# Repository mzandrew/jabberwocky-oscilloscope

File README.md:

# jabberwocky-oscilloscope
an open-source & open-hardware oscilloscope

Jabberwocky is an acronym for Just Another Big Bandwidth Event Recorder With Oscilloscope Capabilities.

It is a combination of hardware designs and software that uses an ASIC switched-capacitor-array ADC to make a handheld, battery/usb powered, 2 channel oscilloscope with an OLED display.

Development on the oscilloscope was started in January, 2008. A design was finalized and a board was fabricated in May of that year.

# overview

The oscilloscope is battery (rechargable LiPoly) or usb powered, has 2 channels of input (DC coupled only), has a 128×124 pixel full-color OLED display. It supports (slightly) advanced triggering or an optional trigger-delay.

The input impedance of this scope is 1MOhm. The analog bandwidth is unknown at this point (and will be until the project is nearly complete). The lab3 can sample billions of times per second, but this oscilloscope will probably only be useful at a much much lower sampling speed. This is due to the choice of input amplifier and multiplexer: The multiplexer has a bandwidth of about 700MHz as does the voltage-feedback operational amplifier.

# files

[PCB schmatic](jabberwocky-PCB-eagle/jabberwocky.schematic.pdf)

[PCB layout](jabberwocky-PCB-eagle/jabberwocky.layout.pdf)

[PCB gerber files](jabberwocky-PCB-eagle/arm7-oscilloscope-gerbers.zip)

# notes

Automatically exported from code.google.com/p/jabberwocky-oscilloscope

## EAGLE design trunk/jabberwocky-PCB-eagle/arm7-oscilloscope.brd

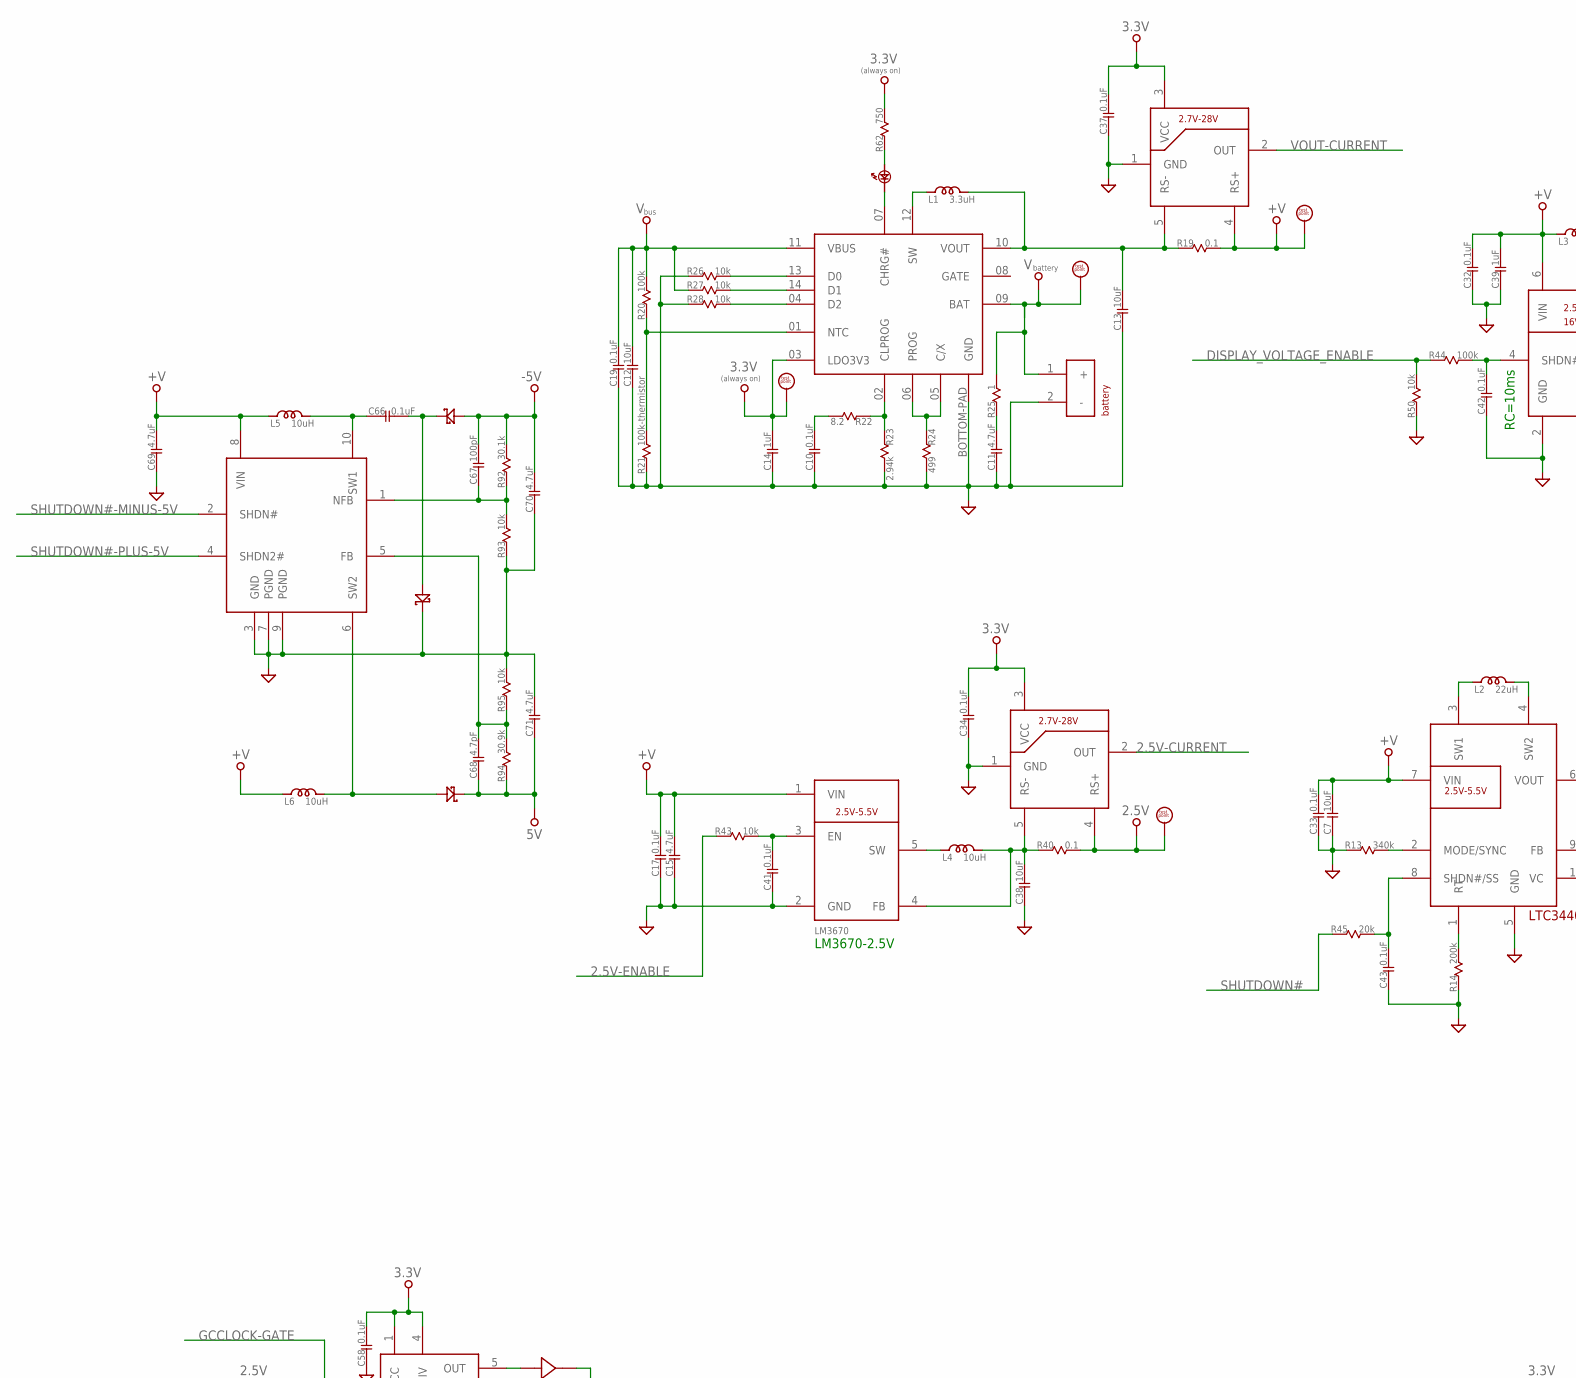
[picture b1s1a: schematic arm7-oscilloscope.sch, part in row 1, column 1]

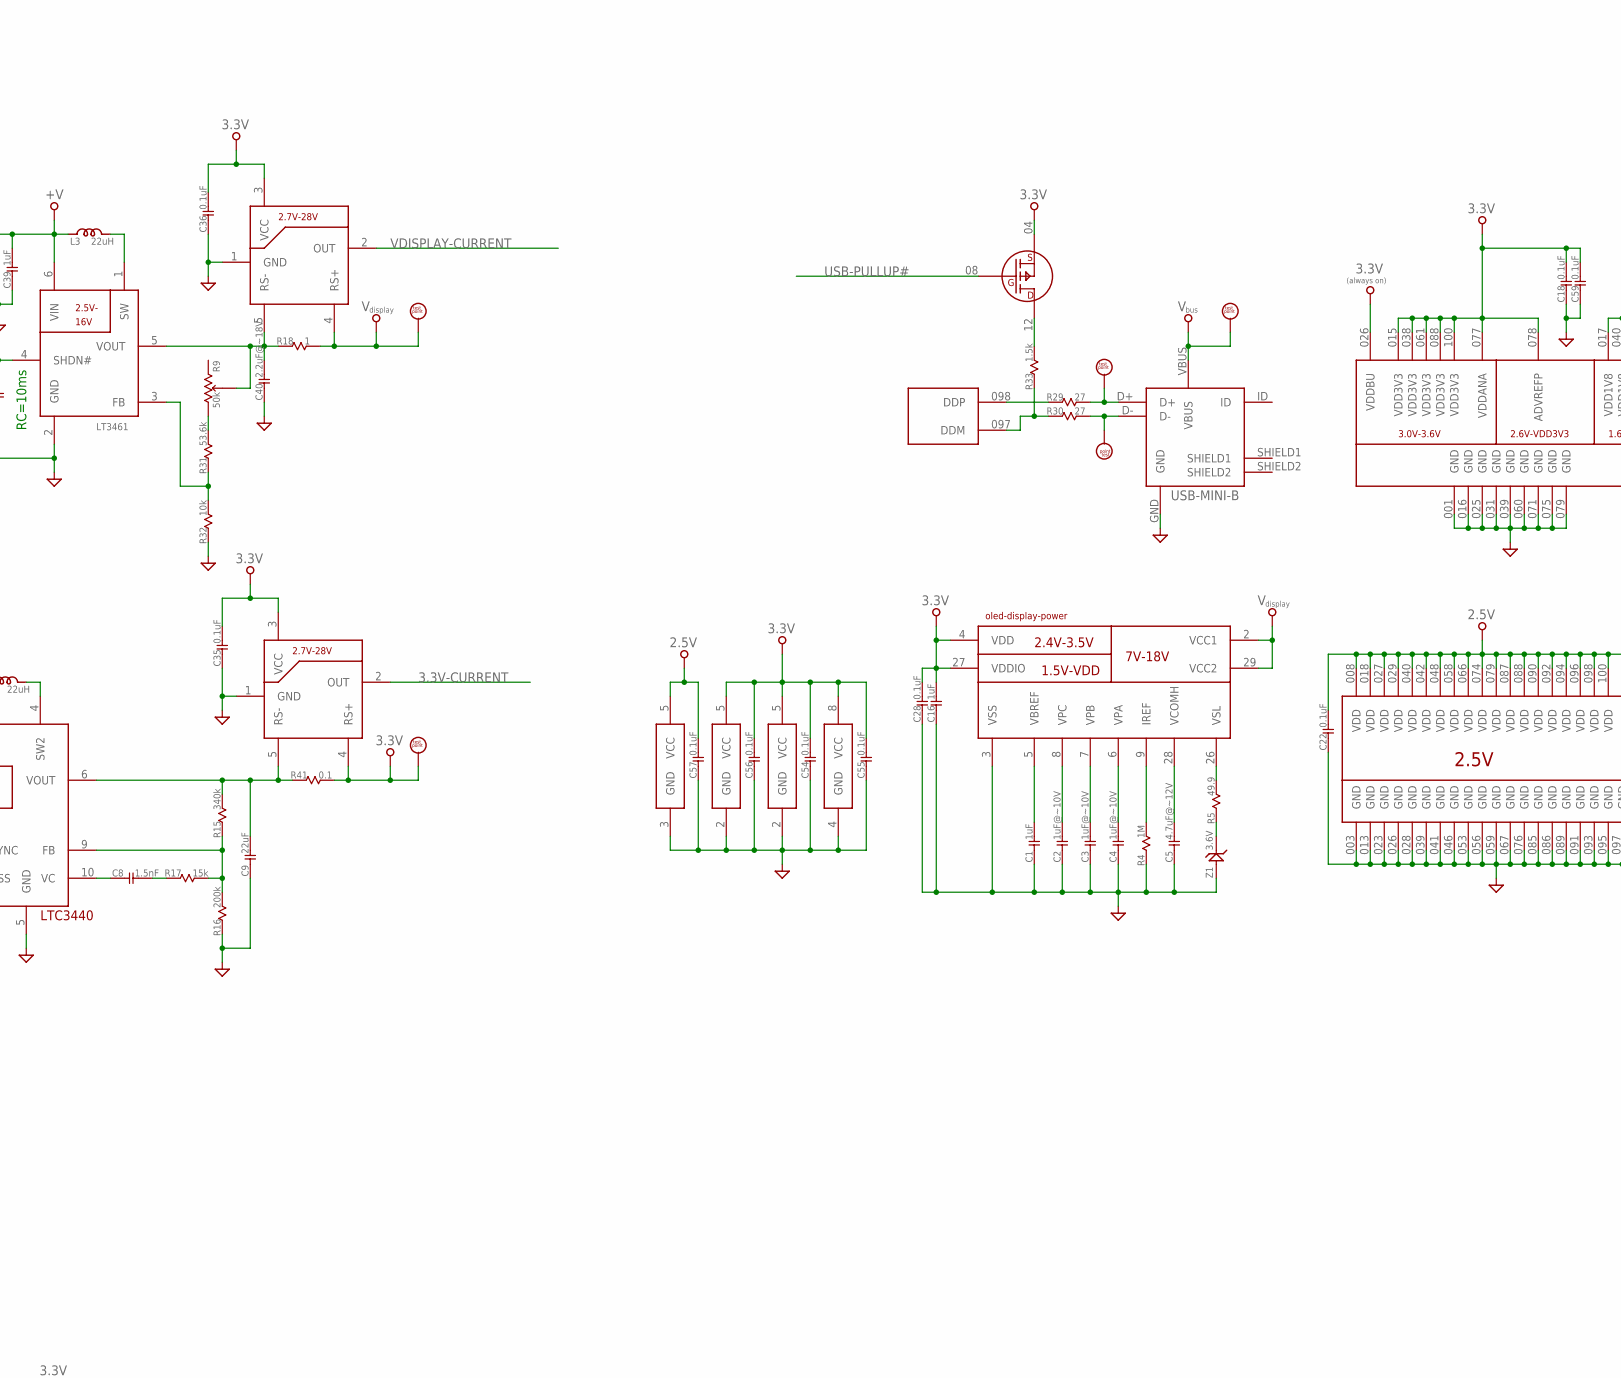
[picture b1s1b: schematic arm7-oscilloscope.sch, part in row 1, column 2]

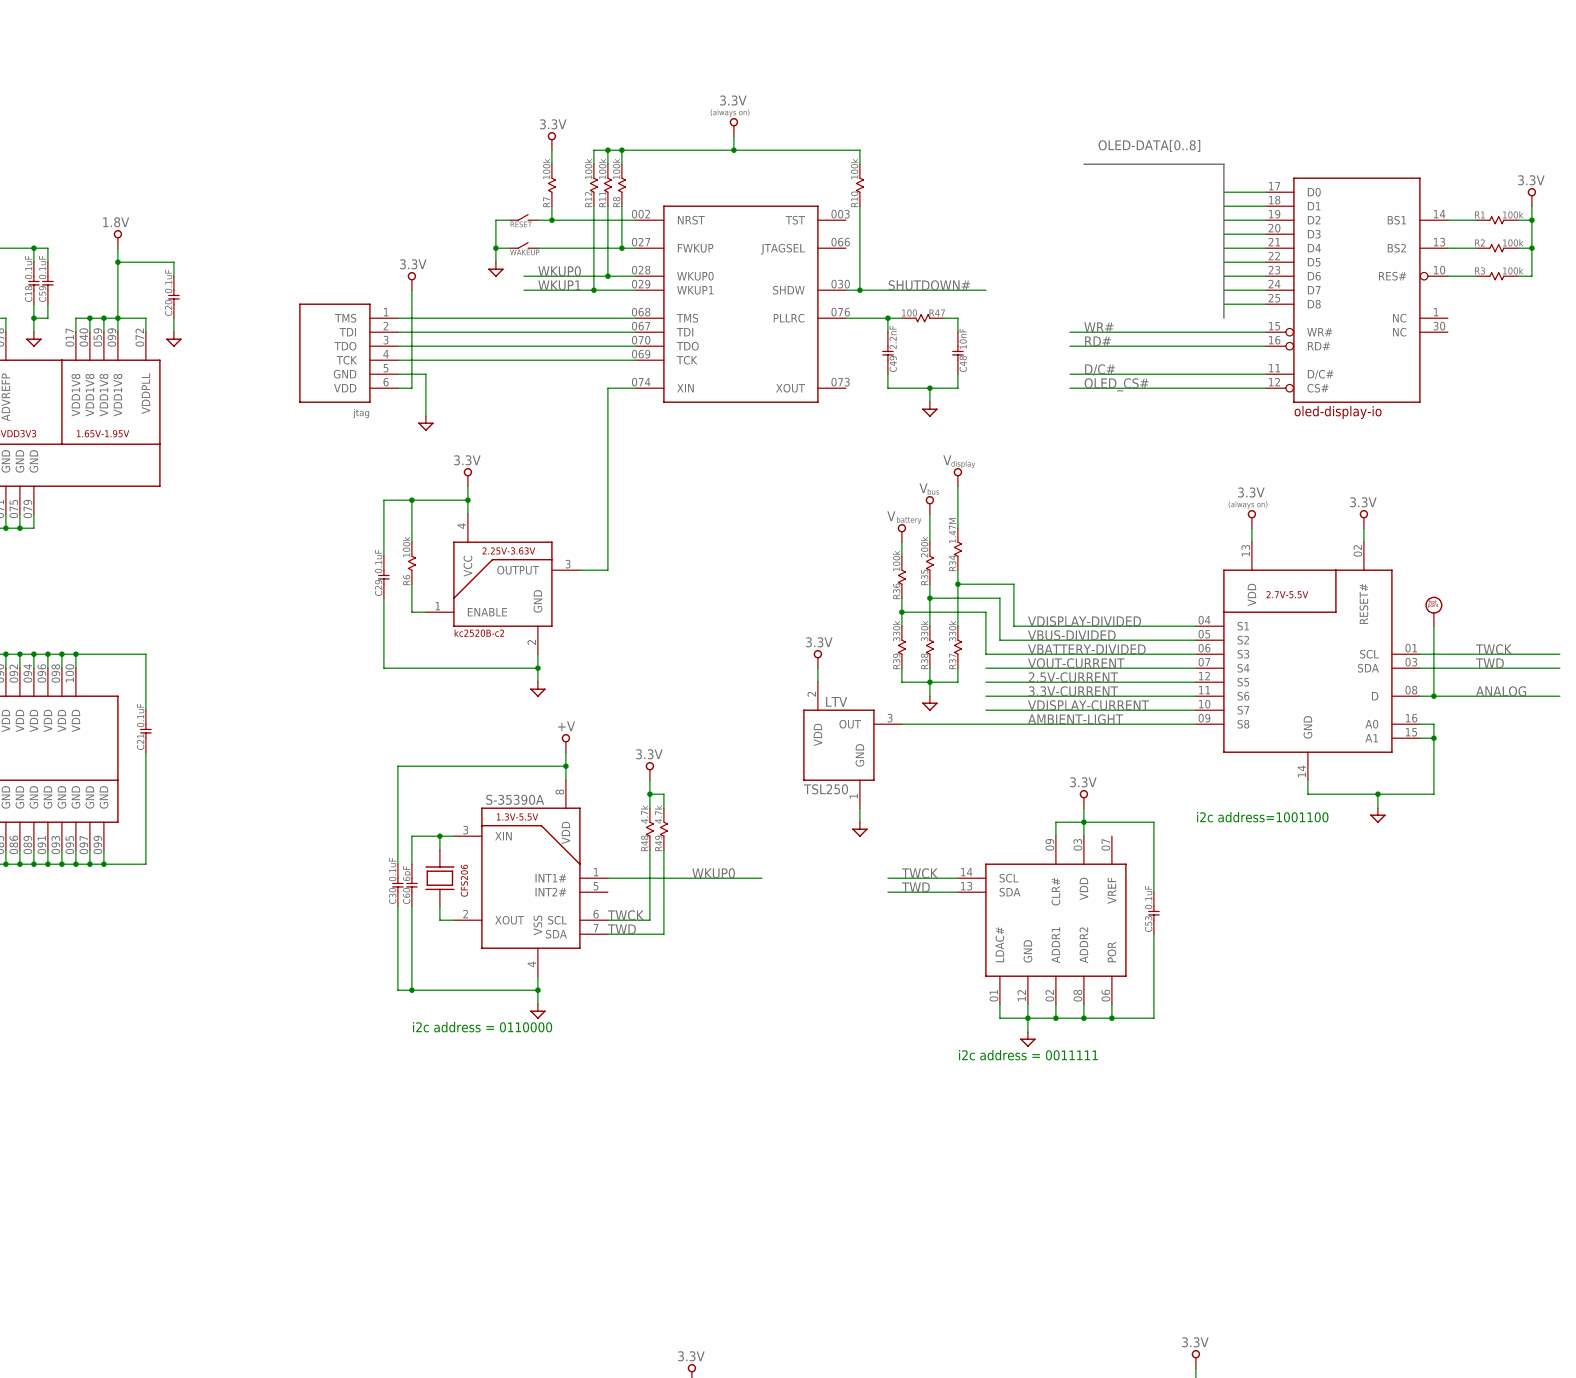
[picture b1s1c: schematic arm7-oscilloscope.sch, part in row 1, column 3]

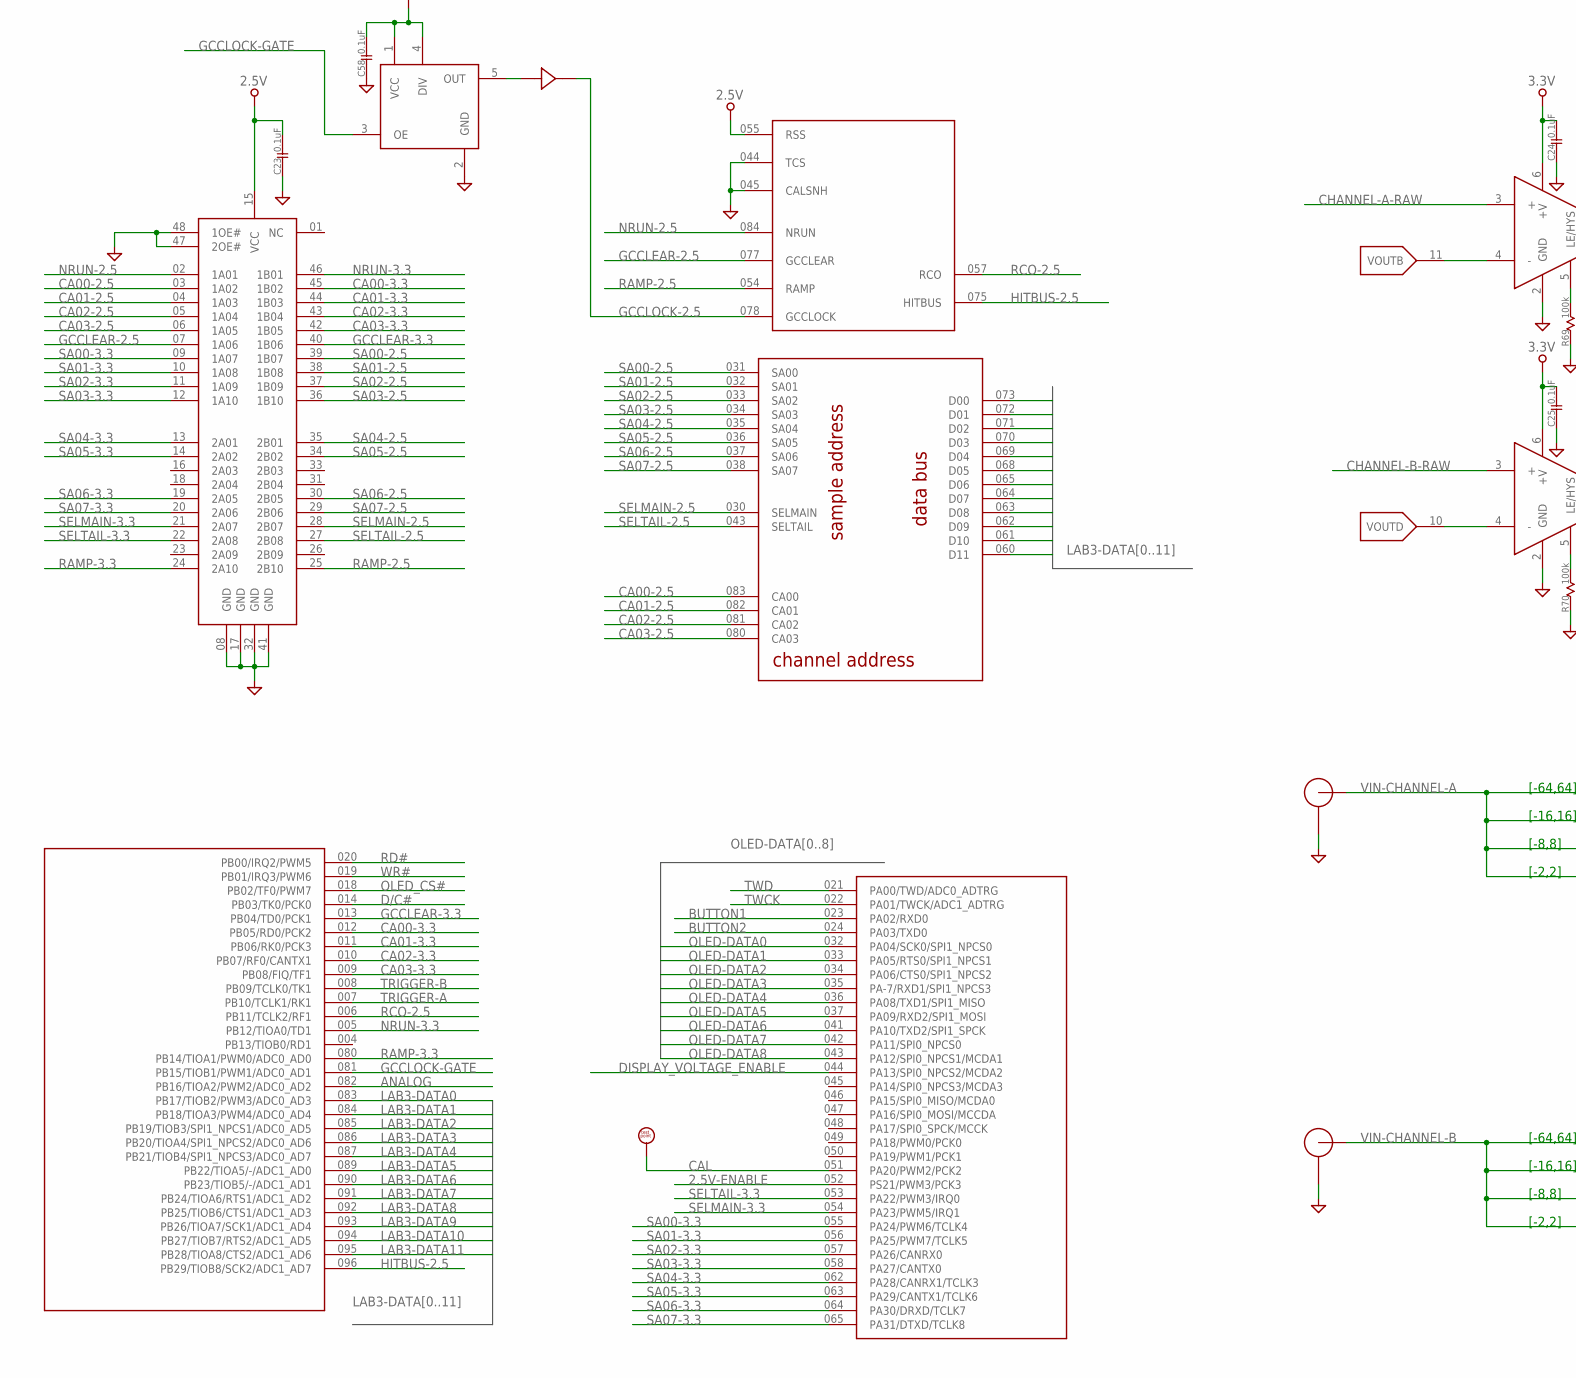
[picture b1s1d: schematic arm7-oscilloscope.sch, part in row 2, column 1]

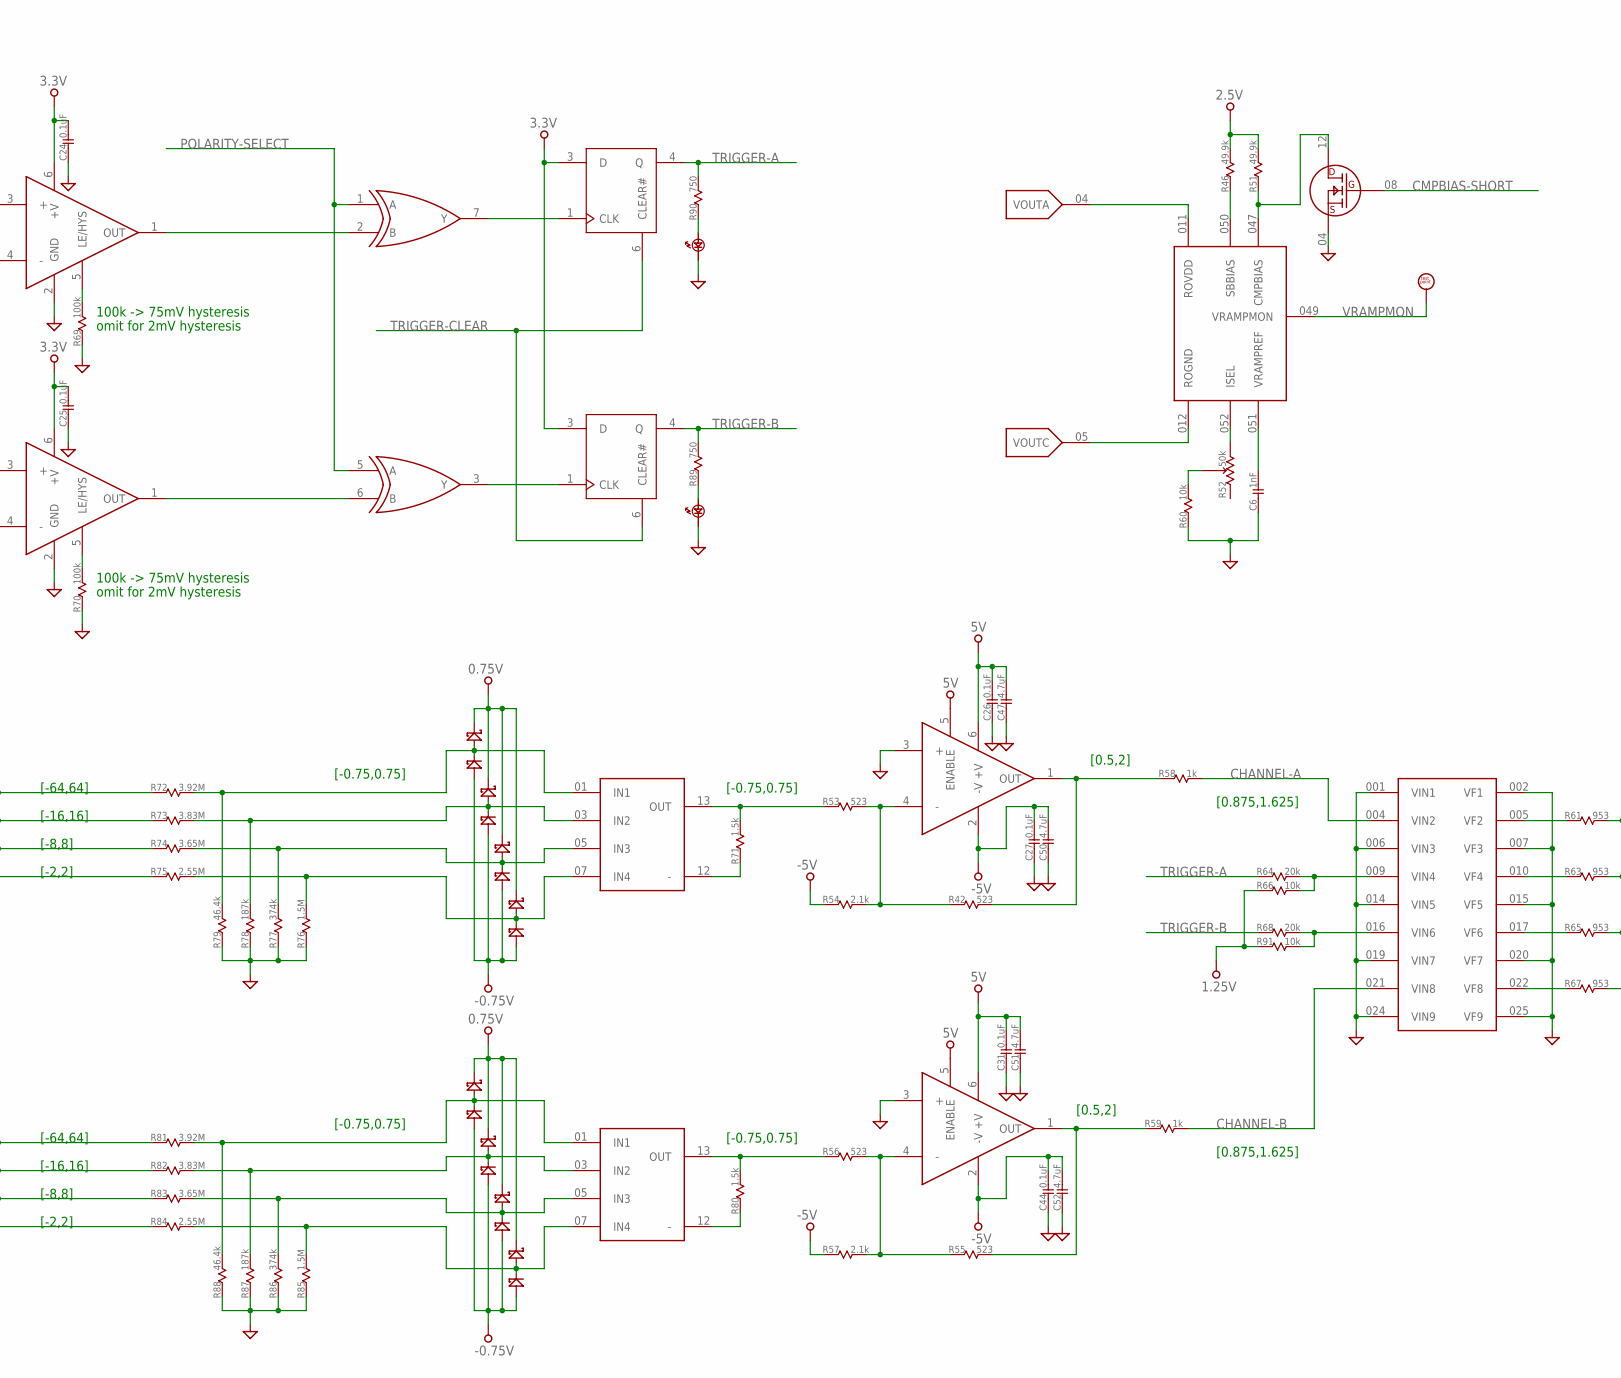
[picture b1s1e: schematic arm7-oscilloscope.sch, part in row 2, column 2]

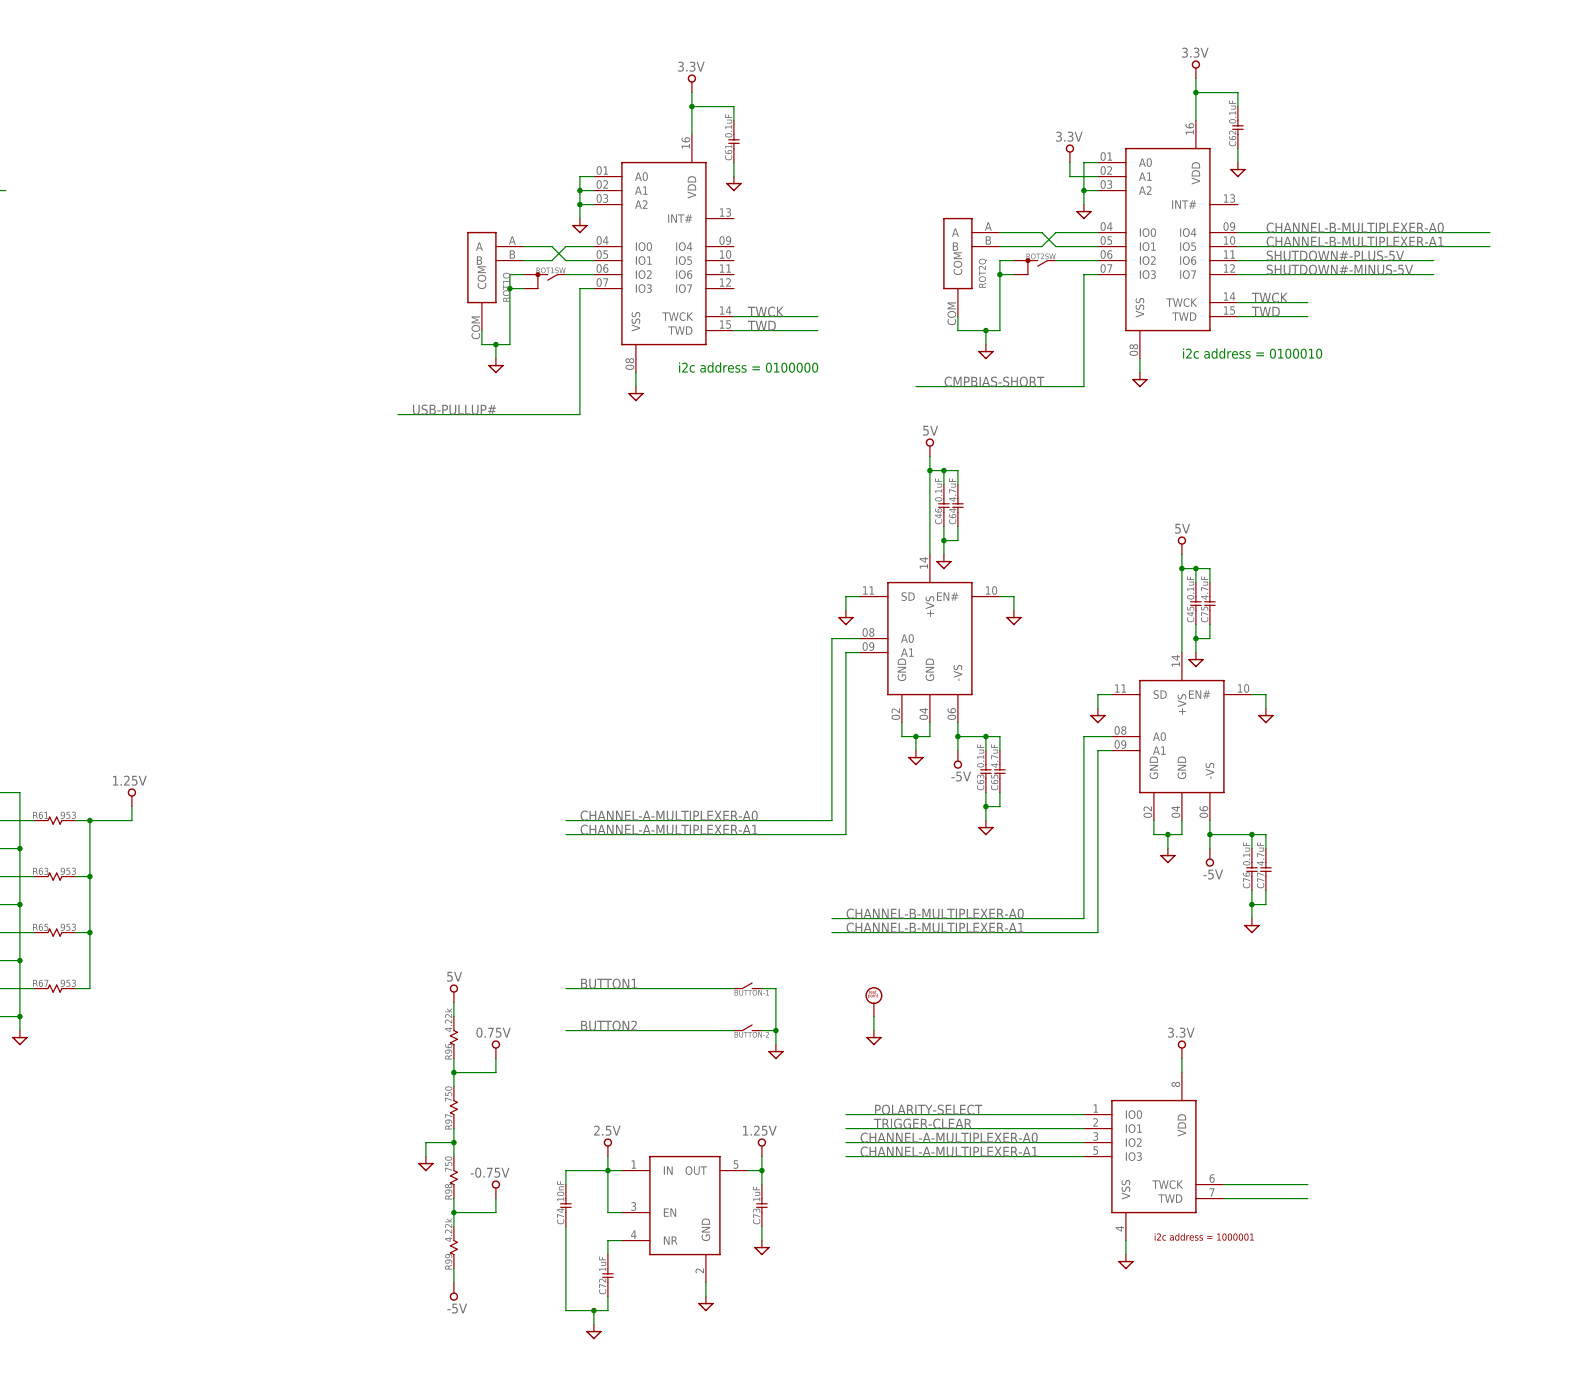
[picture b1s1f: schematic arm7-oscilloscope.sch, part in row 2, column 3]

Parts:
1.25VDC: TPS731XX; SOT-23-5
2.5V, 3.3V, 3.3V-ALWAYS: TEST-POINTSURFACE-MOUNT-1X1; TEST-POINT-SURFACE-MOUNT-1X1
2.5VDC: LM3670; SOT-23-5
3.3VDC: LTC3440; MSOP-10
4DACS: AD56X5R; TSSOP-14
7-18VDC: LT3461; SOT-23-6
+-5VDC: LT1945; MSOP-10
AMP-A: OP-AMP-SOT-23-6; SOT-23-6
AMP-B: OP-AMP-SOT-23-6; SOT-23-6
ANALOG: TEST-POINTSURFACE-MOUNT-1X1; TEST-POINT-SURFACE-MOUNT-1X1
BAT: BATTERY-ON-EXTERNAL-CONNECTOR; S2B-PH-K
BUF1: SN74LVC1G34; SC-70-5
BUTTON-1, BUTTON-2: B3U-1000P
C1, C14, C16, C39, C72, C73: 1uF; 0603
C2, C3, C4: 1uF@~10V; 0603
C5: 4.7uF@~12V; 0805
C6: 1nF; 0603
C7, C12, C13: 10uF; 0805
C8: 1.5nF; 0603
C9: 22uF; 0805
C10, C17, C18, C19, C20, C21, C22, C23, C24, C25, C26, C27, C28, C29, C30, C31, C32, C33, C34, C35, C36, C37, C41, C42, C43, C44, C45, C46, C53, C54, C55, C56, C57, C58, C59, C61, C62, C63, C66, C76: 0.1uF; 0603
C11, C15, C47, C50, C51, C52, C64, C65, C69, C70, C71, C75, C77: 4.7uF; 0603
C38: 10uF; 0603
C40: 2.2uF@~18V; 0805
C48, C74: 10nF; 0603
C49: 2.2nF; 0603
C60: 6pF; 0603
C67: 100pF; 0603
C68: 4.7pF; 0603
CAL: TEST-POINTTHROUGH-HOLE; TEST-POINT-THROUGH-HOLE
CH-A: SMA-SHORT-BARREL-SD-73251-115
CH-B: SMA-SHORT-BARREL-SD-73251-115
CHARGE: LED; 0603
CHRG: LTC4088; DFN-14
CMP-A: ADCMP601; SC-70-6
CMP-B: ADCMP601; SC-70-6
D1, D2, D3: DIODE-SCHOTTKY1005; 1005-DIODE-SCHOTTKY
D4, D5, D6, D7, D8, D9, D10, D11: DIODE-SCHOTTKY-PAIR-ANODE-TO-CATHODE; SOT-23
D+: TEST-POINTSURFACE-MOUNT-1X1; TEST-POINT-SURFACE-MOUNT-1X1
D-: TEST-POINTSURFACE-MOUNT-1X1; TEST-POINT-SURFACE-MOUNT-1X1
FET1: NDS332P; SOT-23
FET2: NDS331N; SOT-23
FFA: 74LVC1G175; SC-70-6
FFB: 74LVC1G175; SC-70-6
GND: TEST-POINTTHROUGH-HOLE; TEST-POINT-THROUGH-HOLE
GPIO1: PCA9536; MSOP-8-OR-TSSOP-8
GPIO2, GPIO3: PCA9554; TSSOP-16
JTAG: HEADER-2MM-2X3-JTAG; HEADER-2MM-2X3
L1: 3.3uH; ELL4-M
L2: 22uH; SD6030
L3: 22uH; 1007
L4, L5, L6: 10uH; 1210
LAB3: LABRADOR3; LQFP-100
LEVEL-SHIFT: SN74CB3T16210; TSSOP-48
LTV: TLS250-BENT; TSL250-BENT
MPEX: ADG728; TSSOP-16
MPEX-A: FHP3194; TSSOP-14
MPEX-B: FHP3194; TSSOP-14
OLED: OLED-DISPLAY-CONNECTOR-2TOP-CONTACTS-IN-USE; XF2M-3015-1A-TOP-CONTACTS-IN-USE
OSC1: KC2520B-C2; OSCILLATOR-2.5X2.0
OSC2: LTC6905; SOT-23-5
R1, R2, R3, R6, R7, R8, R10, R11, R12, R20, R36, R44, R69, R70: 100k; 0603
R4: 1M; 0603
R5: 49.9; 0603
R9, R52: 50k; 3313J-1
R13, R15: 340k; 0603
R14, R16, R35: 200k; 0603
R17: 15k; 0603
R18: 1; 0805
R19, R40, R41: 0.1; 0805
R21: 100k-thermistor; 0603
R22: 8.2; 0603
R23: 2.94k; 0603
R24: 499; 0603
R25: 1; 0603
R26, R27, R28, R32, R43, R50, R60, R66, R91, R93, R95: 10k; 0603
R29, R30: 27; 0603
R31: 53.6k; 0603
R33, R71, R80: 1.5k; 0603
R34: 1.47M; 0603
R37, R38, R39: 330k; 0603
R42, R53, R55, R56: 523; 0603
R45, R64, R68: 20k; 0603
R46, R51: 49.9k; 0603
R47: 100; 0603
R48, R49: 4.7k; 0603
R54, R57: 2.1k; 0603
R58, R59: 1k; 0603
R61, R63, R65, R67: 953; 0603
R62, R89, R90, R97, R98: 750; 0603
R72, R81: 3.92M; 0603
R73, R82: 3.83M; 0603
R74, R83: 3.65M; 0603
R75, R84: 2.55M; 0603
R76, R85: 1.5M; 0603
R77, R86: 374k; 0603
R78, R87: 187k; 0603
R79, R88: 46.4k; 0603
R92: 30.1k; 0603
R94: 30.9k; 0603
R96, R99: 4.22k; 0603
RESET: B3U-1000P
ROT1, ROT2: EVQWK4
RTC: S-35390A; TSSOP-8
TRIGGER-A: LED; 0603
TRIGGER-B: LED; 0603
U$41: CFS206
U$69, U$70, U$71, U$72: MAX4372; SOT-23-5
UC: AT91SAM7A3; LQFP-100
USB: USB-MINI-B; USB-MINI-B-THROUGH-HOLE
VBAT: TEST-POINTSURFACE-MOUNT-1X1; TEST-POINT-SURFACE-MOUNT-1X1
VBUS: TEST-POINTSURFACE-MOUNT-1X1; TEST-POINT-SURFACE-MOUNT-1X1
VDISP: TEST-POINTSURFACE-MOUNT-1X1; TEST-POINT-SURFACE-MOUNT-1X1
VOUT: TEST-POINTSURFACE-MOUNT-1X1; TEST-POINT-SURFACE-MOUNT-1X1
VRAMP: TEST-POINTSURFACE-MOUNT-1X1; TEST-POINT-SURFACE-MOUNT-1X1
WAKEUP: B3U-1000P
XOR: 74LVC2G86; VSSOP-8
Z1: 3.6V; 0603

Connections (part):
0.75V: D4.04 (CATHODE), D5.04 (CATHODE), D6.04 (CATHODE), D7.04 (CATHODE), D8.04 (CATHODE), D9.04 (CATHODE), D10.04 (CATHODE), D11.04 (CATHODE), R96.1, R97.2
1.8V: C20.2, UC.017 (VDD1V8), UC.040 (VDD1V8), UC.059 (VDD1V8), UC.072 (VDDPLL), UC.099 (VDD1V8)
1.25V: 1.25VDC.5 (OUT), C73.2, R61.2, R63.2, R65.2, R66.1, R67.2, R91.1
2.5V: 1.25VDC.1 (IN), 1.25VDC.3 (EN), 2.5V.1, BUF1.5 (VCC), C21.2, C22.2, C23.2, C57.2, C74.2, LAB3.008 (VDD), LAB3.018 (VDD), LAB3.027 (VDD), LAB3.029 (VDD), LAB3.040 (VDD), LAB3.042 (VDD), LAB3.048 (VDD), LAB3.055 (RSS), LAB3.058 (VDD), LAB3.066 (VDD), LAB3.074 (VDD), LAB3.079 (VDD), LAB3.087 (VDD), LAB3.088 (VDD), LAB3.090 (VDD), LAB3.092 (VDD), LAB3.094 (VDD), LAB3.096 (VDD), LAB3.098 (VDD), LAB3.100 (VDD), LEVEL-SHIFT.15 (VCC), R40.2, R46.2, R51.2, U$69.4 (RS+)
2.5V-CURRENT: MPEX.12 (S5), U$69.2 (OUT)
2.5V-ENABLE: R43.1, UC.052 (PS21/PWM3/PCK3)
3.3V: 3.3V.1, 4DACS.03 (VDD), 4DACS.09 (CLR#), C16.2, C18.2, C24.2, C25.2, C28.2, C29.2, C34.2, C35.2, C36.2, C37.2, C53.2, C54.2, C55.2, C56.2, C58.2, C59.2, C61.2, C62.2, CMP-A.6 (+V), CMP-B.6 (+V), FET1.04 (S), FFA.3 (D), FFA.5 (VCC), FFB.3 (D), FFB.5 (VCC), GPIO1.8 (VDD), GPIO2.16 (VDD), GPIO3.02 (A1), GPIO3.16 (VDD), JTAG.6 (VDD), LTV.2 (VDD), MPEX.02 (RESET#), OLED.4 (VDD), OLED.27 (VDDIO), OSC1.4 (VCC), OSC2.1 (VCC), OSC2.4 (DIV), R1.2, R2.2, R3.2, R6.2, R7.2, R41.2, R48.2, R49.2, U$69.3 (VCC), U$70.3 (VCC), U$70.4 (RS+), U$71.3 (VCC), U$72.3 (VCC), UC.015 (VDD3V3), UC.038 (VDD3V3), UC.061 (VDD3V3), UC.077 (VDDANA), UC.078 (ADVREFP), UC.088 (VDD3V3), UC.100 (VDD3V3), XOR.8 (VCC)
3.3V-ALWAYS: 3.3V-ALWAYS.1, C14.2, CHRG.03 (LDO3V3), MPEX.13 (VDD), R8.2, R10.2, R11.2, R12.2, R62.2, UC.026 (VDDBU)
3.3V-CURRENT: MPEX.11 (S6), U$70.2 (OUT)
5V: AMP-A.5 (ENABLE), AMP-A.6 (+V), AMP-B.5 (ENABLE), AMP-B.6 (+V), C26.2, C31.2, C45.2, C46.2, C47.2, C51.2, C64.2, C68.1, C71.1, C75.2, D3.P$2 (CATHODE), MPEX-A.14 (+VS), MPEX-B.14 (+VS), R94.1, R96.2
+V: 2.5VDC.1 (VIN), 3.3VDC.7 (VIN), 7-18VDC.6 (VIN), +-5VDC.8 (VIN), C7.2, C15.2, C17.2, C30.2, C32.2, C33.2, C39.2, C69.2, L3.1, L5.1, L6.1, R19.2, RTC.8 (VDD), U$72.4 (RS+), VOUT.1
-0.75V: D4.08 (ANODE), D5.08 (ANODE), D6.08 (ANODE), D7.08 (ANODE), D8.08 (ANODE), D9.08 (ANODE), D10.08 (ANODE), D11.08 (ANODE), R98.1, R99.2
-5V: AMP-A.2 (-V), AMP-B.2 (-V), C27.2, C44.2, C50.2, C52.2, C63.2, C65.2, C67.2, C70.2, C76.2, C77.2, D1.P$1 (ANODE), MPEX-A.06 (-VS), MPEX-B.06 (-VS), R54.1, R57.1, R92.2, R99.1
AMBIENT-LIGHT: LTV.3 (OUT), MPEX.09 (S8)
ANALOG: ANALOG.1, MPEX.08 (D), UC.082 (PB16/TIOA2/PWM2/ADC0_AD2)
BUTTON1: BUTTON-1.1, UC.023 (PA02/RXD0)
BUTTON2: BUTTON-2.1, UC.024 (PA03/TXD0)
CA00-2.5: LAB3.083 (CA00), LEVEL-SHIFT.03 (1A02)
CA00-3.3: LEVEL-SHIFT.45 (1B02), UC.012 (PB05/RD0/PCK2)
CA01-2.5: LAB3.082 (CA01), LEVEL-SHIFT.04 (1A03)
CA01-3.3: LEVEL-SHIFT.44 (1B03), UC.011 (PB06/RK0/PCK3)
CA02-2.5: LAB3.081 (CA02), LEVEL-SHIFT.05 (1A04)
CA02-3.3: LEVEL-SHIFT.43 (1B04), UC.010 (PB07/RF0/CANTX1)
CA03-2.5: LAB3.080 (CA03), LEVEL-SHIFT.06 (1A05)
CA03-3.3: LEVEL-SHIFT.42 (1B05), UC.009 (PB08/FIQ/TF1)
CAL: CAL.1, UC.051 (PA20/PWM2/PCK2)
CHANNEL-A: LAB3.004 (VIN2), R58.2
CHANNEL-A-MULTIPLEXER-A0: GPIO1.3 (IO2), MPEX-A.08 (A0)
CHANNEL-A-MULTIPLEXER-A1: GPIO1.5 (IO3), MPEX-A.09 (A1)
CHANNEL-A-RAW: AMP-A.1 (OUT), CMP-A.3 (+), R42.2, R58.1
CHANNEL-B: LAB3.021 (VIN8), R59.2
CHANNEL-B-MULTIPLEXER-A0: GPIO3.09 (IO4), MPEX-B.08 (A0)
CHANNEL-B-MULTIPLEXER-A1: GPIO3.10 (IO5), MPEX-B.09 (A1)
CHANNEL-B-RAW: AMP-B.1 (OUT), CMP-B.3 (+), R55.2, R59.1
CHRG: CHARGE.C, CHRG.07 (CHRG#)
CMPBIAS-SHORT: FET2.08 (G), GPIO3.07 (IO3)
D/C#: OLED.11 (D/C#), UC.014 (PB03/TK0/PCK0)
DISPLAY_VOLTAGE_ENABLE: R44.1, R50.2, UC.044 (PA13/SPI0_NPCS2/MCDA2)
GCCLEAR-2.5: LAB3.077 (GCCLEAR), LEVEL-SHIFT.07 (1A06)
GCCLEAR-3.3: LEVEL-SHIFT.40 (1B06), UC.013 (PB04/TD0/PCK1)
GCCLOCK-2.5: BUF1.4 (OUT), LAB3.078 (GCCLOCK)
GCCLOCK-GATE: OSC2.3 (OE), UC.081 (PB15/TIOB1/PWM1/ADC0_AD1)
GND: 1.25VDC.2 (GND), 2.5VDC.2 (GND), 3.3VDC.5 (GND), 4DACS.01 (LDAC#), 4DACS.02 (ADDR1), 4DACS.06 (POR), 4DACS.08 (ADDR2), 4DACS.12 (GND), 7-18VDC.2 (GND), +-5VDC.3 (GND), +-5VDC.7 (PGND), +-5VDC.9 (PGND), AMP-A.3 (+), AMP-B.3 (+), BAT.2 (-), BUF1.3 (GND), BUTTON-1.2, BUTTON-2.2, C1.1, C2.1, C3.1, C4.1, C5.1, C6.1, C7.1, C9.1, C10.1, C11.1, C12.1, C13.1, C14.1, C15.1, C16.1, C17.1, C18.1, C19.1, C20.1, C21.1, C22.1, C23.1, C24.1, C25.1, C26.1, C27.1, C28.1, C29.1, C30.1, C31.1, C32.1, C33.1, C34.1, C35.1, C36.1, C37.1, C38.1, C39.1, C40.1, C41.1, C42.1, C43.1, C44.1, C45.1, C46.1, C47.1, C48.1, C49.1, C50.1, C51.1, C52.1, C53.1, C54.1, C55.1, C56.1, C57.1, C58.1, C59.1, C60.1, C61.1, C62.1, C63.1, C64.1, C65.1, C69.1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
HITBUS-2.5: LAB3.075 (HITBUS), UC.096 (PB29/TIOB8/SCK2/ADC1_AD7)
LAB3-DATA0: LAB3.073 (D00), UC.083 (PB17/TIOB2/PWM3/ADC0_AD3)
LAB3-DATA1: LAB3.072 (D01), UC.084 (PB18/TIOA3/PWM4/ADC0_AD4)
LAB3-DATA2: LAB3.071 (D02), UC.085 (PB19/TIOB3/SPI1_NPCS1/ADC0_AD5)
LAB3-DATA3: LAB3.070 (D03), UC.086 (PB20/TIOA4/SPI1_NPCS2/ADC0_AD6)
LAB3-DATA4: LAB3.069 (D04), UC.087 (PB21/TIOB4/SPI1_NPCS3/ADC0_AD7)
LAB3-DATA5: LAB3.068 (D05), UC.089 (PB22/TIOA5/-/ADC1_AD0)
LAB3-DATA6: LAB3.065 (D06), UC.090 (PB23/TIOB5/-/ADC1_AD1)
LAB3-DATA7: LAB3.064 (D07), UC.091 (PB24/TIOA6/RTS1/ADC1_AD2)
LAB3-DATA8: LAB3.063 (D08), UC.092 (PB25/TIOB6/CTS1/ADC1_AD3)
LAB3-DATA9: LAB3.062 (D09), UC.093 (PB26/TIOA7/SCK1/ADC1_AD4)
LAB3-DATA10: LAB3.061 (D10), UC.094 (PB27/TIOB7/RTS2/ADC1_AD5)
LAB3-DATA11: LAB3.060 (D11), UC.095 (PB28/TIOA8/CTS2/ADC1_AD6)
LTC4088-D0: CHRG.13 (D0), R26.2
LTC4088-D1: CHRG.14 (D1), R27.2
LTC4088-D2: CHRG.04 (D2), R28.2
MAIN_OSCILLATOR: OSC1.3 (OUTPUT), UC.074 (XIN)
unnamed: R7.1, RESET.2, UC.002 (NRST)
unnamed: R8.1, UC.027 (FWKUP), WAKEUP.2
unnamed: +-5VDC.1 (NFB), C67.1, R92.1, R93.2
unnamed: 4DACS.11 (VOUTB), CMP-A.4 (-)
unnamed: R52.1-CCW, R60.2
unnamed: CHARGE.A, R62.1
unnamed: BUF1.2 (IN), OSC2.5 (OUT)
unnamed: OLED.14 (BS1), R1.1
unnamed: 1.25VDC.4 (NR), C72.2
unnamed: LAB3.016 (VIN6), R68.2, R91.2
unnamed: LAB3.009 (VIN4), R64.2, R66.2
unnamed: GPIO2.04 (IO0), ROT1.B
unnamed: GPIO2.05 (IO1), ROT1.A
unnamed: GPIO2.06 (IO2), ROT1.SW2 (1)
unnamed: +-5VDC.5 (FB), C68.2, R94.2, R95.1
unnamed: GPIO3.06 (IO2), ROT2.SW2 (1)
unnamed: GPIO3.04 (IO0), ROT2.B
unnamed: GPIO3.05 (IO1), ROT2.A
unnamed: +-5VDC.6 (SW2), D3.P$1 (ANODE), L6.2
unnamed: 3.3VDC.2 (MODE/SYNC), R13.2
unnamed: 3.3VDC.3 (SW1), L2.1
unnamed: 3.3VDC.1 (RT), R14.2
unnamed: 3.3VDC.4 (SW2), L2.2
unnamed: C8.2, R17.1
unnamed: OLED.13 (BS2), R2.1
unnamed: OLED.10 (RES#), R3.1
unnamed: +-5VDC.10 (SW1), C66.1, L5.2
unnamed: C1.2, OLED.5 (VBREF)
unnamed: C2.2, OLED.8 (VPC)
unnamed: C3.2, OLED.7 (VPB)
unnamed: C4.2, OLED.6 (VPA)
unnamed: OLED.9 (IREF), R4.2
unnamed: C5.2, OLED.28 (VCOMH)
unnamed: OLED.26 (VSL), R5.2
unnamed: R5.1, Z1.2
unnamed: C66.2, D1.P$2 (CATHODE), D2.P$1 (ANODE)
unnamed: 3.3VDC.10 (VC), C8.1
unnamed: OSC1.1 (ENABLE), R6.1
unnamed: FET1.12 (D), R33.2
unnamed: LAB3.052 (ISEL), R52.3-CW
unnamed: 3.3VDC.9 (FB), R15.1, R16.2, R17.2
unnamed: 2.5VDC.4 (FB), C38.2, L4.2, R40.1, U$69.5 (RS-)
unnamed: C60.2, RTC.3 (XIN), U$41.P$1 (1)
unnamed: RTC.2 (XOUT), U$41.P$2 (2)
unnamed: 7-18VDC.1 (SW), L3.2
unnamed: LAB3.050 (SBBIAS), R46.1
unnamed: 7-18VDC.3 (FB), R31.1, R32.2
unnamed: FET2.12 (D), LAB3.047 (CMPBIAS), R51.1
unnamed: C6.2, LAB3.051 (VRAMPREF)
unnamed: 4DACS.04 (VOUTA), LAB3.011 (ROVDD)
unnamed: CHRG.01 (NTC), R20.1, R21.2
unnamed: CHRG.12 (SW), L1.1
unnamed: 4DACS.05 (VOUTC), LAB3.012 (ROGND)
unnamed: C10.2, R22.2
unnamed: CHRG.02 (CLPROG), R22.1, R23.1
unnamed: CHRG.05 (C/X), CHRG.06 (PROG), R24.1
unnamed: C49.2, R47.2, UC.076 (PLLRC)
unnamed: C11.2, R25.1
unnamed: CMP-A.1 (OUT), XOR.2 (B)
unnamed: C48.2, R47.1
unnamed: D+.1, R29.2, USB.D+
unnamed: D-.1, R30.2, USB.D-
unnamed: R29.1, UC.098 (DDP)
unnamed: R30.1, R33.1, UC.097 (DDM)
unnamed: JTAG.1 (TMS), UC.068 (TMS)
unnamed: JTAG.2 (TDI), UC.067 (TDI)
unnamed: JTAG.3 (TDO), UC.070 (TDO)
unnamed: 3.3VDC.6 (VOUT), C9.2, R15.2, R41.1, U$70.5 (RS-)
unnamed: JTAG.4 (TCK), UC.069 (TCK)
unnamed: 2.5VDC.3 (EN), C41.2, R43.2
unnamed: R9.3-CW, R31.2
unnamed: 7-18VDC.4 (SHDN#), C42.2, R44.2
unnamed: 3.3VDC.8 (SHDN#/SS), C43.2, R45.2
unnamed: FFA.1 (CLK), XOR.7 (Y)
unnamed: FFB.1 (CLK), XOR.3 (Y)
unnamed: CMP-B.1 (OUT), XOR.6 (B)
unnamed: AMP-A.4 (-), R42.1, R53.2, R54.2
unnamed: AMP-B.4 (-), R55.1, R56.2, R57.2
unnamed: 4DACS.10 (VOUTD), CMP-B.4 (-)
unnamed: LAB3.005 (VF2), R61.1
unnamed: LAB3.010 (VF4), R63.1
unnamed: LAB3.017 (VF6), R65.1
unnamed: LAB3.022 (VF8), R67.1
unnamed: CMP-A.5 (LE/HYS), R69.2
unnamed: CMP-B.5 (LE/HYS), R70.2
unnamed: MPEX-A.13 (OUT), R53.1, R71.2
unnamed: MPEX-A.12 (-), R71.1
unnamed: D4.12 (ANODE-CATHODE), MPEX-A.01 (IN1), R72.2, R79.2
unnamed: D6.12 (ANODE-CATHODE), MPEX-A.05 (IN3), R74.2, R77.2
unnamed: D7.12 (ANODE-CATHODE), MPEX-A.07 (IN4), R75.2, R76.2
unnamed: MPEX-B.13 (OUT), R56.1, R80.2
unnamed: MPEX-B.12 (-), R80.1
unnamed: D8.12 (ANODE-CATHODE), MPEX-B.01 (IN1), R81.2, R88.2
unnamed: D9.12 (ANODE-CATHODE), MPEX-B.03 (IN2), R82.2, R87.2
unnamed: D10.12 (ANODE-CATHODE), MPEX-B.05 (IN3), R83.2, R86.2
unnamed: D11.12 (ANODE-CATHODE), MPEX-B.07 (IN4), R84.2, R85.2
unnamed: R90.1, TRIGGER-A.A
unnamed: 2.5VDC.5 (SW), L4.1
unnamed: R89.1, TRIGGER-B.A
unnamed: D5.12 (ANODE-CATHODE), MPEX-A.03 (IN2), R73.2, R78.2
NRUN-2.5: LAB3.084 (NRUN), LEVEL-SHIFT.02 (1A01)
NRUN-3.3: LEVEL-SHIFT.46 (1B01), UC.005 (PB12/TIOA0/TD1)
OLED-DATA0: OLED.17 (D0), UC.032 (PA04/SCK0/SPI1_NPCS0)
OLED-DATA1: OLED.18 (D1), UC.033 (PA05/RTS0/SPI1_NPCS1)
OLED-DATA2: OLED.19 (D2), UC.034 (PA06/CTS0/SPI1_NPCS2)
OLED-DATA3: OLED.20 (D3), UC.035 (PA-7/RXD1/SPI1_NPCS3)
OLED-DATA4: OLED.21 (D4), UC.036 (PA08/TXD1/SPI1_MISO)
OLED-DATA5: OLED.22 (D5), UC.037 (PA09/RXD2/SPI1_MOSI)
OLED-DATA6: OLED.23 (D6), UC.041 (PA10/TXD2/SPI1_SPCK)
OLED-DATA7: OLED.24 (D7), UC.042 (PA11/SPI0_NPCS0)
OLED-DATA8: OLED.25 (D8), UC.043 (PA12/SPI0_NPCS1/MCDA1)
OLED_CS#: OLED.12 (CS#), UC.018 (PB02/TF0/PWM7)
POLARITY-SELECT: GPIO1.1 (IO0), XOR.1 (A), XOR.5 (A)
RAMP-2.5: LAB3.054 (RAMP), LEVEL-SHIFT.25 (2B10)
RAMP-3.3: LEVEL-SHIFT.24 (2A10), UC.080 (PB14/TIOA1/PWM0/ADC0_AD0)
RCO-2.5: LAB3.057 (RCO), UC.006 (PB11/TCLK2/RF1)
RD#: OLED.16 (RD#), UC.020 (PB00/IRQ2/PWM5)
SA00-2.5: LAB3.031 (SA00), LEVEL-SHIFT.39 (1B07)
SA00-3.3: LEVEL-SHIFT.09 (1A07), UC.055 (PA24/PWM6/TCLK4)
SA01-2.5: LAB3.032 (SA01), LEVEL-SHIFT.38 (1B08)
SA01-3.3: LEVEL-SHIFT.10 (1A08), UC.056 (PA25/PWM7/TCLK5)
SA02-2.5: LAB3.033 (SA02), LEVEL-SHIFT.37 (1B09)
SA02-3.3: LEVEL-SHIFT.11 (1A09), UC.057 (PA26/CANRX0)
SA03-2.5: LAB3.034 (SA03), LEVEL-SHIFT.36 (1B10)
SA03-3.3: LEVEL-SHIFT.12 (1A10), UC.058 (PA27/CANTX0)
SA04-2.5: LAB3.035 (SA04), LEVEL-SHIFT.35 (2B01)
SA04-3.3: LEVEL-SHIFT.13 (2A01), UC.062 (PA28/CANRX1/TCLK3)
SA05-2.5: LAB3.036 (SA05), LEVEL-SHIFT.34 (2B02)
SA05-3.3: LEVEL-SHIFT.14 (2A02), UC.063 (PA29/CANTX1/TCLK6)
SA06-2.5: LAB3.037 (SA06), LEVEL-SHIFT.30 (2B05)
SA06-3.3: LEVEL-SHIFT.19 (2A05), UC.064 (PA30/DRXD/TCLK7)
SA07-2.5: LAB3.038 (SA07), LEVEL-SHIFT.29 (2B06)
SA07-3.3: LEVEL-SHIFT.20 (2A06), UC.065 (PA31/DTXD/TCLK8)
SELMAIN-2.5: LAB3.030 (SELMAIN), LEVEL-SHIFT.28 (2B07)
SELMAIN-3.3: LEVEL-SHIFT.21 (2A07), UC.054 (PA23/PWM5/IRQ1)
SELTAIL-2.5: LAB3.043 (SELTAIL), LEVEL-SHIFT.27 (2B08)
SELTAIL-3.3: LEVEL-SHIFT.22 (2A08), UC.053 (PA22/PWM3/IRQ0)
SHUTDOWN#: R10.1, R45.1, UC.030 (SHDW)
SHUTDOWN#-MINUS-5V: +-5VDC.2 (SHDN#), GPIO3.12 (IO7)
SHUTDOWN#-PLUS-5V: +-5VDC.4 (SHDN2#), GPIO3.11 (IO6)
TRIGGER-A: FFA.4 (Q), R64.1, R90.2, UC.007 (PB10/TCLK1/RK1)
TRIGGER-B: FFB.4 (Q), R68.1, R89.2, UC.008 (PB09/TCLK0/TK1)
TRIGGER-CLEAR: FFA.6 (CLEAR#), FFB.6 (CLEAR#), GPIO1.2 (IO1)
TWCK: 4DACS.14 (SCL), GPIO1.6 (TWCK), GPIO2.14 (TWCK), GPIO3.14 (TWCK), MPEX.01 (SCL), R48.1, RTC.6 (SCL), UC.022 (PA01/TWCK/ADC1_ADTRG)
TWD: 4DACS.13 (SDA), GPIO1.7 (TWD), GPIO2.15 (TWD), GPIO3.15 (TWD), MPEX.03 (SDA), R49.1, RTC.7 (SDA), UC.021 (PA00/TWD/ADC0_ADTRG)
USB-PULLUP#: FET1.08 (G), GPIO2.07 (IO3)
VBAT: C13.2, CHRG.10 (VOUT), L1.2, R19.1, U$72.5 (RS-)
VBATTERY: BAT.1 (+), CHRG.09 (BAT), R25.2, R36.2, VBAT.1
VBATTERY-DIVIDED: MPEX.06 (S3), R36.1, R39.2
VBUS: C12.2, C19.2, CHRG.11 (VBUS), R20.2, R27.1, R35.2, USB.VBUS, VBUS.1
VBUS-DIVIDED: MPEX.05 (S2), R35.1, R38.2
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
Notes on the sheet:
RC=10ms
i2c address=1001100
LM3670-2.5V
i2c address = 0110000
100k -> 75mV hysteresis
omit for 2mV hysteresis
[-64,64]
[-16,16]
[-8,8]
[-2,2]
[0.875,1.625]
i2c address = 0011111
[-0.75,0.75]
[0.5,2]
i2c address = 0100000
i2c address = 0100010
